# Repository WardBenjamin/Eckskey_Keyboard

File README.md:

# Eckskey

The Eckskey (pronounced "x key") keyboard is an open source 74% mechanical keyboard, designed with an emphasis on electrical correctness and manufacturability, and with some fun tricks.

## Design Philosophy

Throughout the design, electrical correctness will be emphasized, including proper differential pair routing (within the constraints of a two layer design), ground planes, current carrying capacity, and oscillator routing. The board is manufacturable with 6mil trace/space, accomplishable with 1oz two layer designs by local vendors in your area (including the United States) as well as at the cheapest Chinese vendors like JLCPCB, PCBway, and AllPCB.

The base keyboard is designed to be made in two pieces, meaning that it can be assembled in a small/cheap reflow oven like a ControLEO 3 toaster oven conversion or the common Chinese T962 variants. This adds a small amount of BOM cost and would probably increase the cost at quantity, but enables wider access.

This keyboard is NOT meant to be assembled by the typical r/MK hobbyist - it includes QFN and 0603 parts which require a stencil and a pair of tweezers and a pick and place machine to assemble reasonably. You CAN solder these by hand or with hot air but it is difficult. 

## Fun tricks

In total, the base keyboard is a 74% design, meaning that it retains alphanumerics, function keys (F1-F12), and symbols. In addition, the bottom row has been modified to add a left function key (FN) between left control and META/Windows and a right print screen key between menu and right control. Since it still uses a normal 6.25U spacebar, the right keys in the bottom of the row have each been shrunk to 1U. The function keys have been shifted leftwards and collapsed in order to make space for 1U insert and delete keys above backspace. This retains all common functionality of a 100% keyboard except for nav cluster, media keys, and numpad.

The base keyboard includes an integrated USB hub to allow for additional modules to be connected. Two modules will be made - a numpad and nav cluster+media keys. These will technically be separate keyboards, connected via USB-C and magnetic mounting, and can be used standalone as well. These keyboards also have access to the function key by taking advantage of the SBU pins of the USB-C connectors which are normally unused in a USB 1.1/2.0 implementation.

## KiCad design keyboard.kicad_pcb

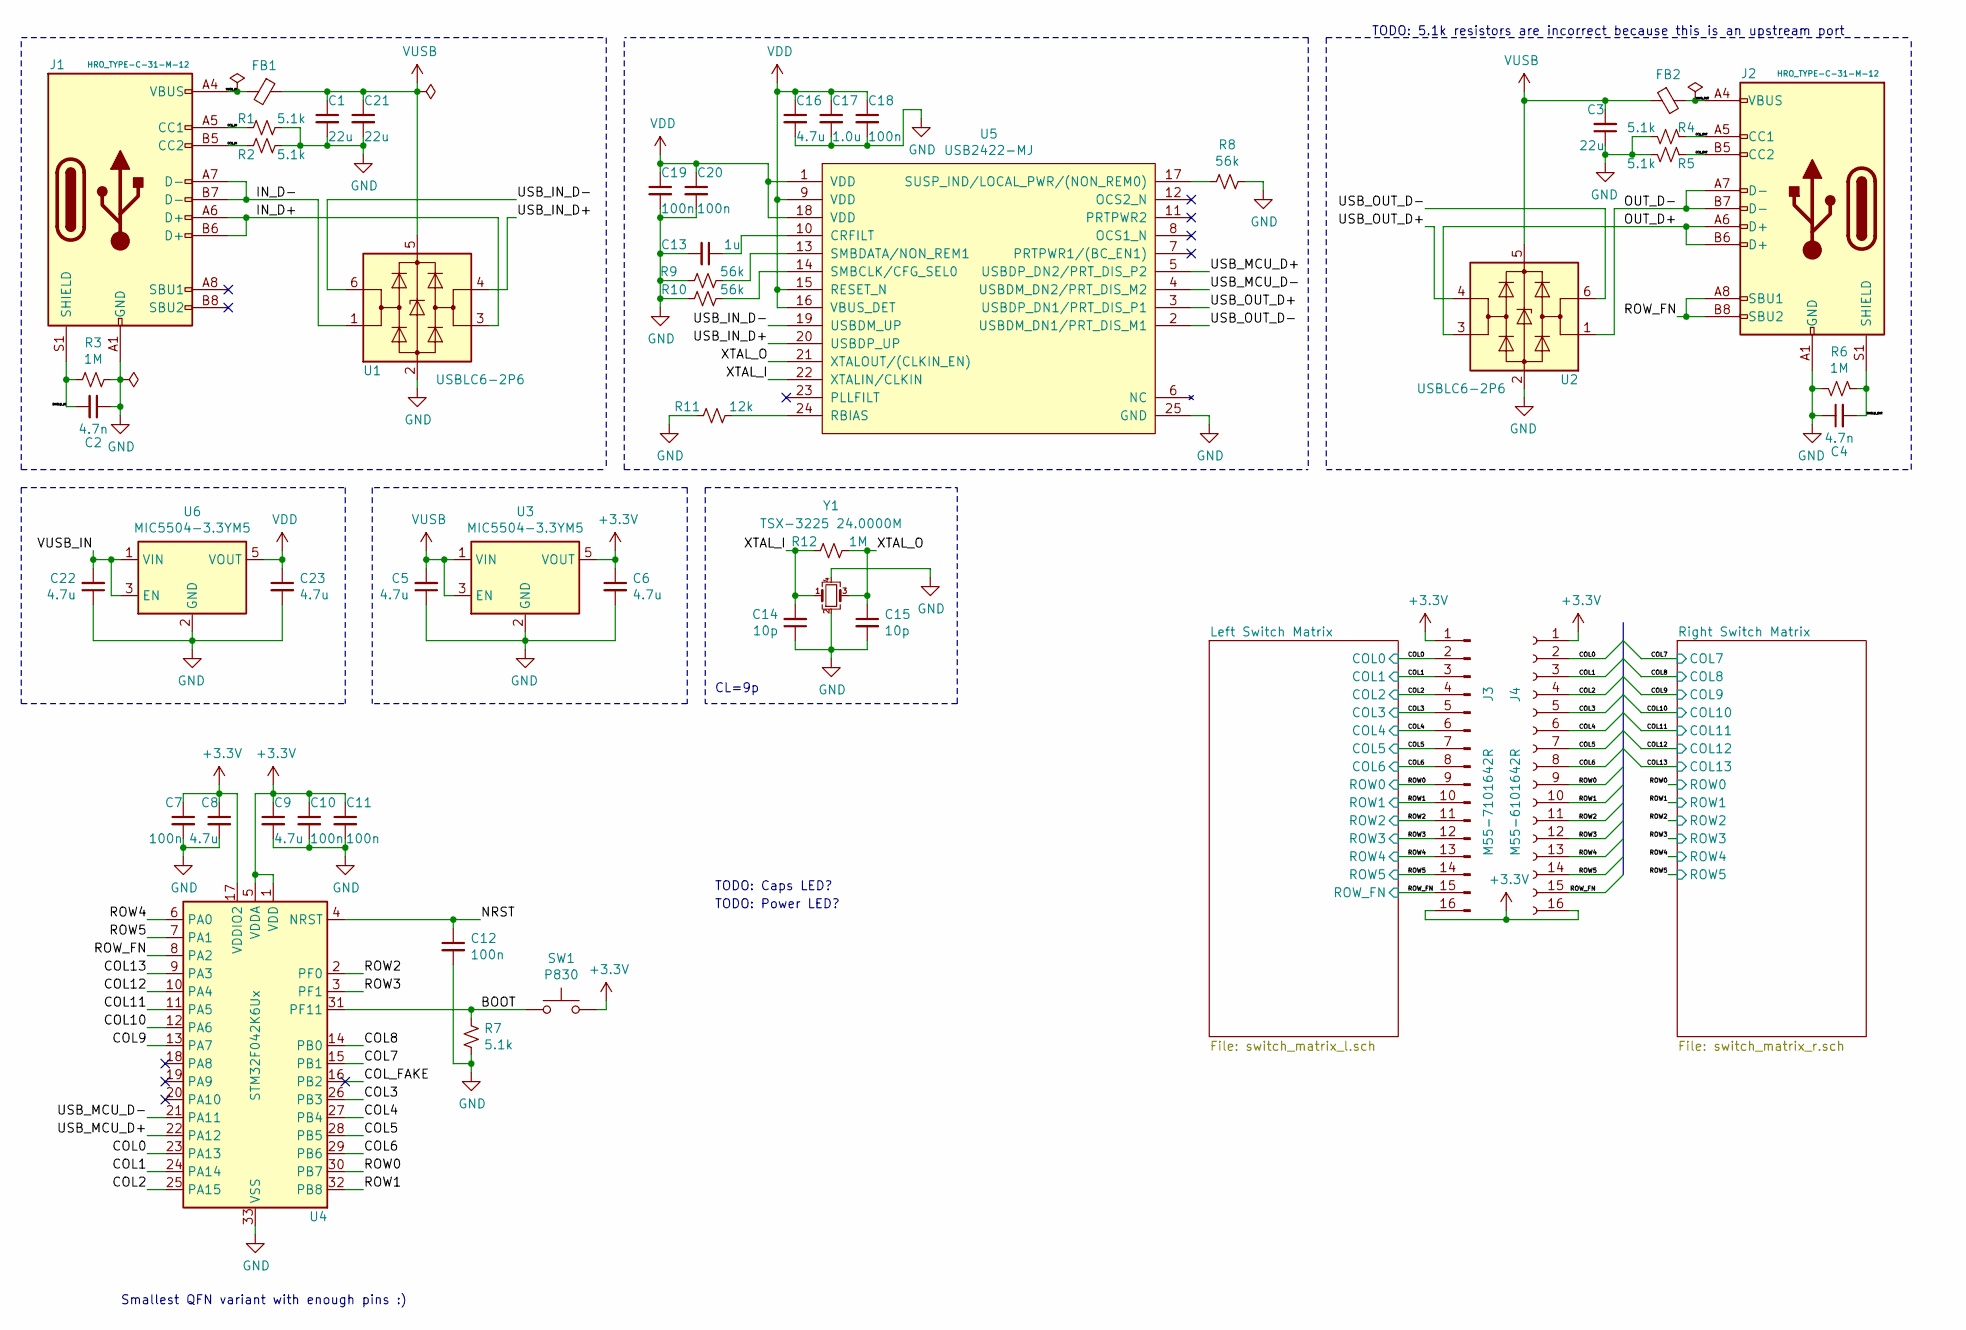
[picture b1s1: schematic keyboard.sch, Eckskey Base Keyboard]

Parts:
C1, C3, C21: 22u; C_0603_1608Metric
C2, C4: 4.7n; C_0603_1608Metric
C5, C6, C8, C9, C16, C22, C23: 4.7u; C_0603_1608Metric
C7, C10, C11, C12, C18, C19, C20: 100n; C_0603_1608Metric
C13: 1u; C_0603_1608Metric
C14, C15: 10p; C_0603_1608Metric
C17: 1.0u; C_0603_1608Metric
FB1, FB2: Ferrite_Bead_Small; L_0603_1608Metric
J1, J2: HRO_TYPE-C-31-M-12; USB_C_Receptacle_HRO_TYPE-C-31-M-12
J3: M55-7101642R; M557101642R
J4: M55-6101642R; M556101642R
R1, R2, R4, R5, R7: 5.1k; R_0603_1608Metric
R3, R6, R12: 1M; R_0603_1608Metric
R8, R9, R10: 56k; R_0603_1608Metric
R11: 12k; R_0603_1608Metric
SW1: P830; SW_SPST_PTS830
U1, U2: USBLC6-2P6; SOT-666
U3, U6: MIC5504-3.3YM5; SOT-23-5
U4: STM32F042K6Ux; QFN-32-1EP_5x5mm_P0.5mm_EP3.45x3.45mm
U5: USB2422-MJ; QFN-24-1EP_4x4mm_P0.5mm_EP2.7x2.7mm_ThermalVias
Y1: TSX-3225 24.0000M; Crystal_SMD_SeikoEpson_TSX3225-4Pin_3.2x2.5mm

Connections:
+3V3: C6.1, C7.1, C8.1, C9.1, C10.1, C11.1, J3.1, J3.16, J4.1, J4.16, SW1.2, U3.5 (VOUT), U4.1 (VDD), U4.5 (VDDA), U4.17 (VDDIO2); also elsewhere on the board
/BOOT: R7.1, SW1.1, U4.31 (PF11)
/CC1_IN: J1.A5 (CC1), R1.2
/CC1_OUT: J2.A5 (CC1), R4.2
/CC2_IN: J1.B5 (CC2), R2.2
/CC2_OUT: J2.B5 (CC2), R5.2
/COL0: J3.2, J4.2, U4.23 (PA13); also elsewhere on the board
/COL1: J3.3, J4.3, U4.24 (PA14); also elsewhere on the board
/COL2: J3.4, J4.4, U4.25 (PA15); also elsewhere on the board
/COL3: J3.5, J4.5, U4.26 (PB3); also elsewhere on the board
/COL4: J3.6, J4.6, U4.27 (PB4); also elsewhere on the board
/COL5: J3.7, J4.7, U4.28 (PB5); also elsewhere on the board
/COL6: J3.8, J4.8, U4.29 (PB6); also elsewhere on the board
/COL7: U4.15 (PB1); also elsewhere on the board
/COL8: U4.14 (PB0); also elsewhere on the board
/COL9: U4.13 (PA7); also elsewhere on the board
/COL10: U4.12 (PA6); also elsewhere on the board
/COL11: U4.11 (PA5); also elsewhere on the board
/COL12: U4.10 (PA4); also elsewhere on the board
/COL13: U4.9 (PA3); also elsewhere on the board
/IN_D+: J1.A6 (D+), J1.B6 (D+), U1.3 (I/O2)
/IN_D-: J1.A7 (D-), J1.B7 (D-), U1.1 (I/O1)
/NRST: C12.1, U4.4 (NRST)
/OUT_D+: J2.A6 (D+), J2.B6 (D+), U2.3 (I/O2)
/OUT_D-: J2.A7 (D-), J2.B7 (D-), U2.1 (I/O1)
/ROW0: J3.9, J4.9, U4.30 (PB7); also elsewhere on the board
/ROW1: J3.10, J4.10, U4.32 (PB8); also elsewhere on the board
/ROW2: J3.11, J4.11, U4.2 (PF0); also elsewhere on the board
/ROW3: J3.12, J4.12, U4.3 (PF1); also elsewhere on the board
/ROW4: J3.13, J4.13, U4.6 (PA0); also elsewhere on the board
/ROW5: J3.14, J4.14, U4.7 (PA1); also elsewhere on the board
/ROW_FN: J2.A8 (SBU1), J2.B8 (SBU2), J3.15, J4.15, U4.8 (PA2); also elsewhere on the board
/SHIELD_IN: C2.2, J1.S1 (SHIELD), R3.2
/SHIELD_OUT: C4.2, J2.S1 (SHIELD), R6.2
/USB_IN_D+: U1.4 (I/O2), U5.20 (USBDP_UP)
/USB_IN_D-: U1.6 (I/O1), U5.19 (USBDM_UP)
/USB_MCU_D+: U4.22 (PA12), U5.5 (USBDP_DN2/PRT_DIS_P2)
/USB_MCU_D-: U4.21 (PA11), U5.4 (USBDM_DN2/PRT_DIS_M2)
/USB_OUT_D+: U2.4 (I/O2), U5.3 (USBDP_DN1/PRT_DIS_P1)
/USB_OUT_D-: U2.6 (I/O1), U5.2 (USBDM_DN1/PRT_DIS_M1)
/VUSB_IN: C22.2, FB1.2, J1.A4 (VBUS), J1.A9 (VBUS), J1.B4 (VBUS), J1.B9 (VBUS), U6.1 (VIN), U6.3 (EN)
/VUSB_OUT: FB2.2, J2.A4 (VBUS), J2.A9 (VBUS), J2.B4 (VBUS), J2.B9 (VBUS)
/XTAL_I: C14.2, R12.2, U5.22 (XTALIN/CLKIN), Y1.1
/XTAL_O: C15.1, R12.1, U5.21 (XTALOUT/(CLKIN_EN)), Y1.3
GND: C1.2, C2.1, C3.1, C4.1, C5.1, C6.2, C7.2, C8.2, C9.2, C10.2, C11.2, C12.2, C13.2, C14.1, C15.2, C16.2, C17.2, C18.2, C19.2, C20.2, C21.2, C22.1, C23.2, J1.A1 (GND), J1.A12 (GND), J1.B1 (GND), J1.B12 (GND), J2.A1 (GND), J2.A12 (GND), J2.B1 (GND), J2.B12 (GND), R1.1, R2.1, R3.1, R4.1, R5.1, R6.1, R7.2, R8.1, R9.2, R10.2, R11.2, U1.2 (GND), U2.2 (GND), U3.2 (GND), U4.33 (VSS), U5.25 (GND), U6.2 (GND), Y1.2, Y1.4
unnamed: C13.1, U5.10 (CRFILT)
unnamed: R8.2, U5.17 (SUSP_IND/LOCAL_PWR/(NON_REM0))
unnamed: R9.1, U5.13 (SMBDATA/NON_REM1)
unnamed: R10.1, U5.14 (SMBCLK/CFG_SEL0)
unnamed: R11.1, U5.24 (RBIAS)
VDD: C16.1, C17.1, C18.1, C19.1, C20.1, C23.1, U5.1 (VDD), U5.9 (VDD), U5.15 (RESET_N), U5.16 (VBUS_DET), U5.18 (VDD), U6.5 (VOUT)
VUSB: C1.1, C3.2, C5.2, C21.1, FB1.1, FB2.1, U1.5 (VBUS), U2.5 (VBUS), U3.1 (VIN), U3.3 (EN)

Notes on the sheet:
Smallest QFN variant with enough pins :)
CL=9p
TODO: Caps LED?
TODO: 5.1k resistors are incorrect because this is an upstream port
TODO: Power LED?

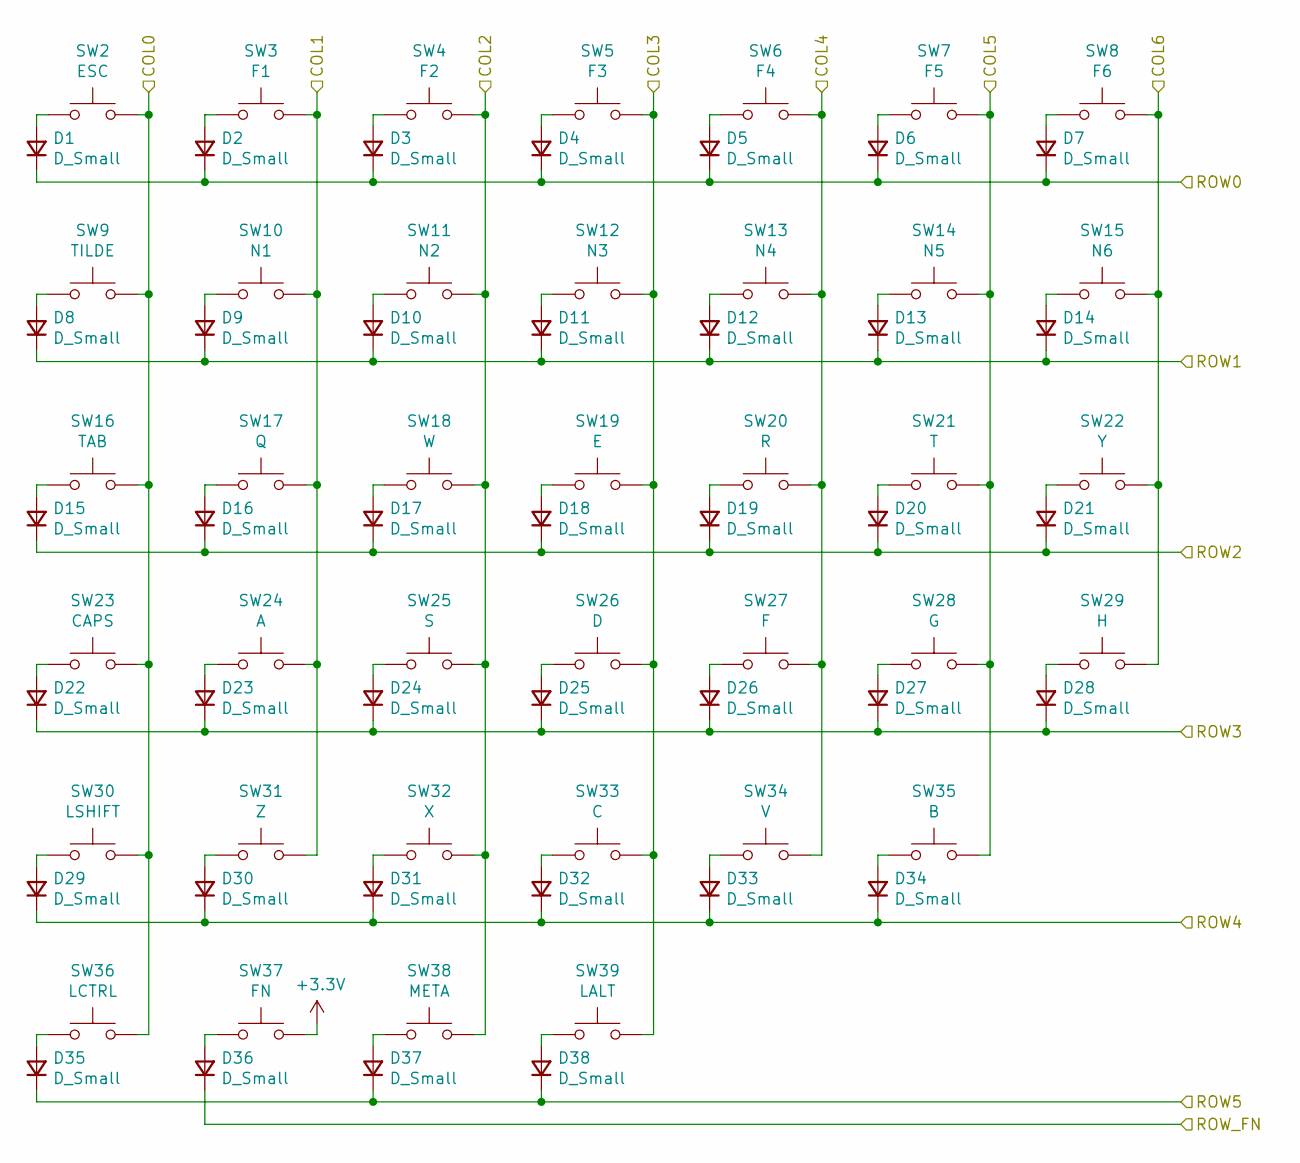
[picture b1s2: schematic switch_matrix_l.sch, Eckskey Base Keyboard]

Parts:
D1, D2, D3, D4, D5, D6, D7, D8, D9, D10, D11, D12, D13, D14, D15, D16, D17, D18, D19, D20, D21, D22, D23, D24, D25, D26, D27, D28, D29, D30, D31, D32, D33, D34, D35, D36, D37, D38: D_Small; D_SOD-123F
SW2: ESC; MX-1U
SW3: F1; MX-1U
SW4: F2; MX-1U
SW5: F3; MX-1U
SW6: F4; MX-1U
SW7: F5; MX-1U
SW8: F6; MX-1U
SW9: TILDE; MX-1U
SW10: N1; MX-1U
SW11: N2; MX-1U
SW12: N3; MX-1U
SW13: N4; MX-1U
SW14: N5; MX-1U
SW15: N6; MX-1U
SW16: TAB; MX-1.5U
SW17: Q; MX-1U
SW18: W; MX-1U
SW19: E; MX-1U
SW20: R; MX-1U
SW21: T; MX-1U
SW22: Y; MX-1U
SW23: CAPS; MX-1.75U
SW24: A; MX-1U
SW25: S; MX-1U
SW26: D; MX-1U
SW27: F; MX-1U
SW28: G; MX-1U
SW29: H; MX-1U
SW30: LSHIFT; MX-2.25U
SW31: Z; MX-1U
SW32: X; MX-1U
SW33: C; MX-1U
SW34: V; MX-1U
SW35: B; MX-1U
SW36: LCTRL; MX-1.25U
SW37: FN; MX-1U
SW38: META; MX-1.25U
SW39: LALT; MX-1.25U

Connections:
+3V3: SW37.2; also elsewhere on the board
/COL0: SW2.2, SW9.2, SW16.2, SW23.2, SW30.2, SW36.2; also elsewhere on the board
/COL1: SW3.2, SW10.2, SW17.2, SW24.2, SW31.2; also elsewhere on the board
/COL2: SW4.2, SW11.2, SW18.2, SW25.2, SW32.2, SW38.2; also elsewhere on the board
/COL3: SW5.2, SW12.2, SW19.2, SW26.2, SW33.2, SW39.2; also elsewhere on the board
/COL4: SW6.2, SW13.2, SW20.2, SW27.2, SW34.2; also elsewhere on the board
/COL5: SW7.2, SW14.2, SW21.2, SW28.2, SW35.2; also elsewhere on the board
/COL6: SW8.2, SW15.2, SW22.2, SW29.2; also elsewhere on the board
/ROW0: D1.1 (K), D2.1 (K), D3.1 (K), D4.1 (K), D5.1 (K), D6.1 (K), D7.1 (K); also elsewhere on the board
/ROW1: D8.1 (K), D9.1 (K), D10.1 (K), D11.1 (K), D12.1 (K), D13.1 (K), D14.1 (K); also elsewhere on the board
/ROW2: D15.1 (K), D16.1 (K), D17.1 (K), D18.1 (K), D19.1 (K), D20.1 (K), D21.1 (K); also elsewhere on the board
/ROW3: D22.1 (K), D23.1 (K), D24.1 (K), D25.1 (K), D26.1 (K), D27.1 (K), D28.1 (K); also elsewhere on the board
/ROW4: D29.1 (K), D30.1 (K), D31.1 (K), D32.1 (K), D33.1 (K), D34.1 (K); also elsewhere on the board
/ROW5: D35.1 (K), D37.1 (K), D38.1 (K); also elsewhere on the board
/ROW_FN: D36.1 (K); also elsewhere on the board
unnamed: D1.2 (A), SW2.1
unnamed: D2.2 (A), SW3.1
unnamed: D3.2 (A), SW4.1
unnamed: D4.2 (A), SW5.1
unnamed: D5.2 (A), SW6.1
unnamed: D6.2 (A), SW7.1
unnamed: D7.2 (A), SW8.1
unnamed: D8.2 (A), SW9.1
unnamed: D9.2 (A), SW10.1
unnamed: D10.2 (A), SW11.1
unnamed: D11.2 (A), SW12.1
unnamed: D12.2 (A), SW13.1
unnamed: D13.2 (A), SW14.1
unnamed: D14.2 (A), SW15.1
unnamed: D15.2 (A), SW16.1
unnamed: D16.2 (A), SW17.1
unnamed: D17.2 (A), SW18.1
unnamed: D18.2 (A), SW19.1
unnamed: D19.2 (A), SW20.1
unnamed: D20.2 (A), SW21.1
unnamed: D21.2 (A), SW22.1
unnamed: D22.2 (A), SW23.1
unnamed: D23.2 (A), SW24.1
unnamed: D24.2 (A), SW25.1
unnamed: D25.2 (A), SW26.1
unnamed: D26.2 (A), SW27.1
unnamed: D27.2 (A), SW28.1
unnamed: D28.2 (A), SW29.1
unnamed: D29.2 (A), SW30.1
unnamed: D30.2 (A), SW31.1
unnamed: D31.2 (A), SW32.1
unnamed: D32.2 (A), SW33.1
unnamed: D33.2 (A), SW34.1
unnamed: D34.2 (A), SW35.1
unnamed: D35.2 (A), SW36.1
unnamed: D36.2 (A), SW37.1
unnamed: D37.2 (A), SW38.1
unnamed: D38.2 (A), SW39.1

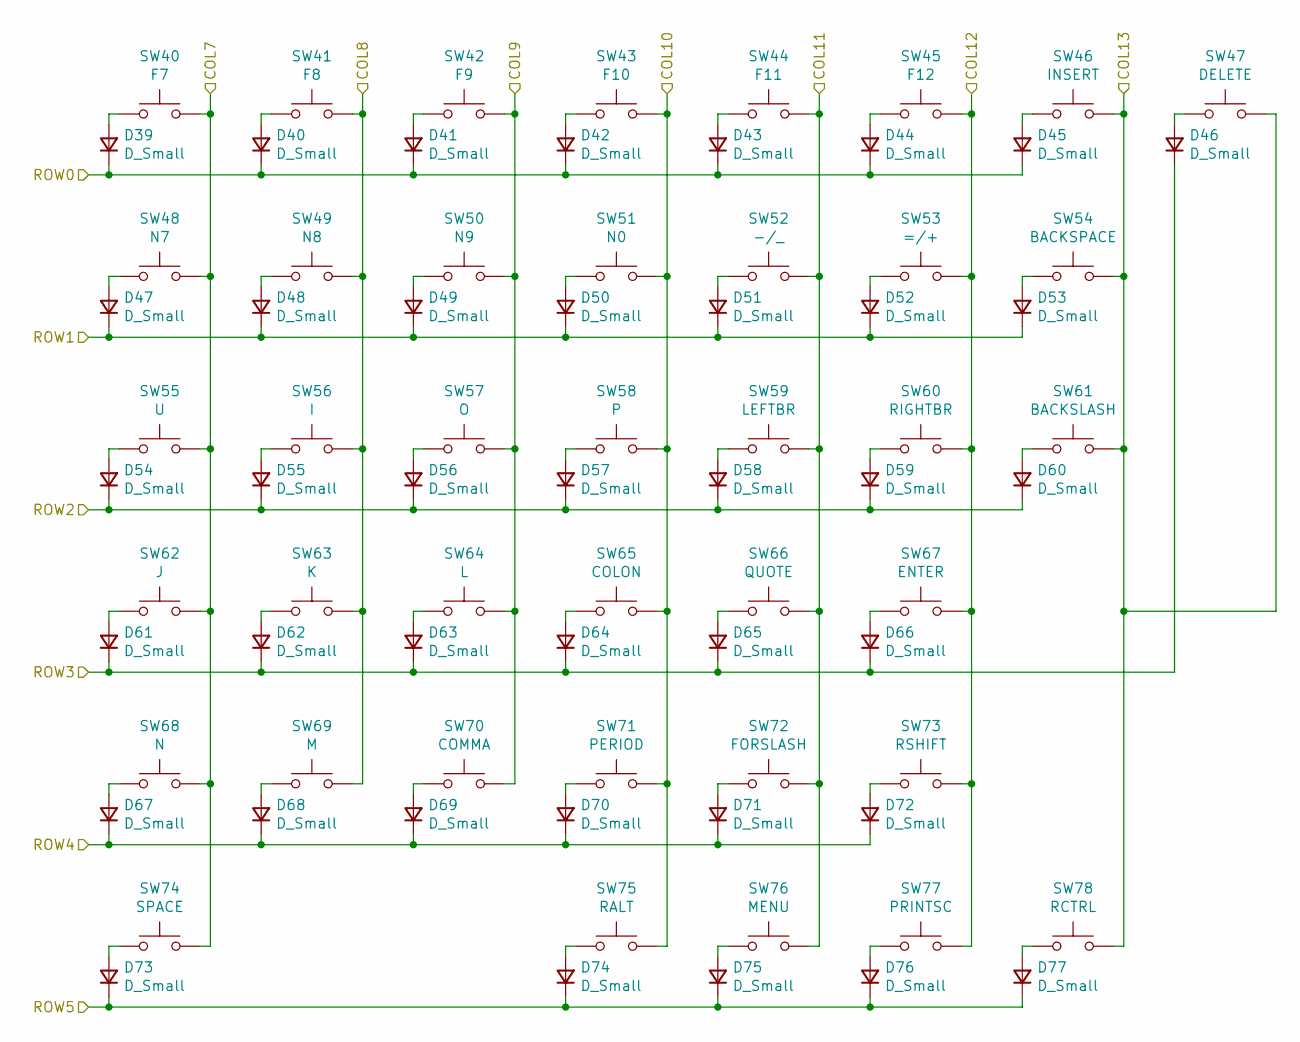
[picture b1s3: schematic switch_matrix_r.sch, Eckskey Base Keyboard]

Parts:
D39, D40, D41, D42, D43, D44, D45, D46, D47, D48, D49, D50, D51, D52, D53, D54, D55, D56, D57, D58, D59, D60, D61, D62, D63, D64, D65, D66, D67, D68, D69, D70, D71, D72, D73, D74, D75, D76, D77: D_Small; D_SOD-123F
SW40: F7; MX-1U
SW41: F8; MX-1U
SW42: F9; MX-1U
SW43: F10; MX-1U
SW44: F11; MX-1U
SW45: F12; MX-1U
SW46: INSERT; MX-1U
SW47: DELETE; MX-1U
SW48: N7; MX-1U
SW49: N8; MX-1U
SW50: N9; MX-1U
SW51: N0; MX-1U
SW52: -/_; MX-1U
SW53: =/+; MX-1U
SW54: BACKSPACE; MX-2U
SW55: U; MX-1U
SW56: I; MX-1U
SW57: O; MX-1U
SW58: P; MX-1U
SW59: LEFTBR; MX-1U
SW60: RIGHTBR; MX-1U
SW61: BACKSLASH; MX-1.5U
SW62: J; MX-1U
SW63: K; MX-1U
SW64: L; MX-1U
SW65: COLON; MX-1U
SW66: QUOTE; MX-1U
SW67: ENTER; MX-2.25U
SW68: N; MX-1U
SW69: M; MX-1U
SW70: COMMA; MX-1U
SW71: PERIOD; MX-1U
SW72: FORSLASH; MX-1U
SW73: RSHIFT; MX-2.75U
SW74: SPACE; MX-6.25U
SW75: RALT; MX-1U
SW76: MENU; MX-1U
SW77: PRINTSC; MX-1U
SW78: RCTRL; MX-1U

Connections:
/COL7: SW40.2, SW48.2, SW55.2, SW62.2, SW68.2, SW74.2; also elsewhere on the board
/COL8: SW41.2, SW49.2, SW56.2, SW63.2, SW69.2; also elsewhere on the board
/COL9: SW42.2, SW50.2, SW57.2, SW64.2, SW70.2; also elsewhere on the board
/COL10: SW43.2, SW51.2, SW58.2, SW65.2, SW71.2, SW75.2; also elsewhere on the board
/COL11: SW44.2, SW52.2, SW59.2, SW66.2, SW72.2, SW76.2; also elsewhere on the board
/COL12: SW45.2, SW53.2, SW60.2, SW67.2, SW73.2, SW77.2; also elsewhere on the board
/COL13: SW46.2, SW47.2, SW54.2, SW61.2, SW78.2; also elsewhere on the board
/ROW0: D39.1 (K), D40.1 (K), D41.1 (K), D42.1 (K), D43.1 (K), D44.1 (K), D45.1 (K); also elsewhere on the board
/ROW1: D47.1 (K), D48.1 (K), D49.1 (K), D50.1 (K), D51.1 (K), D52.1 (K), D53.1 (K); also elsewhere on the board
/ROW2: D54.1 (K), D55.1 (K), D56.1 (K), D57.1 (K), D58.1 (K), D59.1 (K), D60.1 (K); also elsewhere on the board
/ROW3: D46.1 (K), D61.1 (K), D62.1 (K), D63.1 (K), D64.1 (K), D65.1 (K), D66.1 (K); also elsewhere on the board
/ROW4: D67.1 (K), D68.1 (K), D69.1 (K), D70.1 (K), D71.1 (K), D72.1 (K); also elsewhere on the board
/ROW5: D73.1 (K), D74.1 (K), D75.1 (K), D76.1 (K), D77.1 (K); also elsewhere on the board
unnamed: D39.2 (A), SW40.1
unnamed: D40.2 (A), SW41.1
unnamed: D41.2 (A), SW42.1
unnamed: D42.2 (A), SW43.1
unnamed: D43.2 (A), SW44.1
unnamed: D44.2 (A), SW45.1
unnamed: D45.2 (A), SW46.1
unnamed: D46.2 (A), SW47.1
unnamed: D47.2 (A), SW48.1
unnamed: D48.2 (A), SW49.1
unnamed: D49.2 (A), SW50.1
unnamed: D50.2 (A), SW51.1
unnamed: D51.2 (A), SW52.1
unnamed: D52.2 (A), SW53.1
unnamed: D53.2 (A), SW54.1
unnamed: D54.2 (A), SW55.1
unnamed: D55.2 (A), SW56.1
unnamed: D56.2 (A), SW57.1
unnamed: D57.2 (A), SW58.1
unnamed: D58.2 (A), SW59.1
unnamed: D59.2 (A), SW60.1
unnamed: D60.2 (A), SW61.1
unnamed: D61.2 (A), SW62.1
unnamed: D62.2 (A), SW63.1
unnamed: D63.2 (A), SW64.1
unnamed: D64.2 (A), SW65.1
unnamed: D65.2 (A), SW66.1
unnamed: D66.2 (A), SW67.1
unnamed: D67.2 (A), SW68.1
unnamed: D68.2 (A), SW69.1
unnamed: D69.2 (A), SW70.1
unnamed: D70.2 (A), SW71.1
unnamed: D71.2 (A), SW72.1
unnamed: D72.2 (A), SW73.1
unnamed: D73.2 (A), SW74.1
unnamed: D74.2 (A), SW75.1
unnamed: D75.2 (A), SW76.1
unnamed: D76.2 (A), SW77.1
unnamed: D77.2 (A), SW78.1

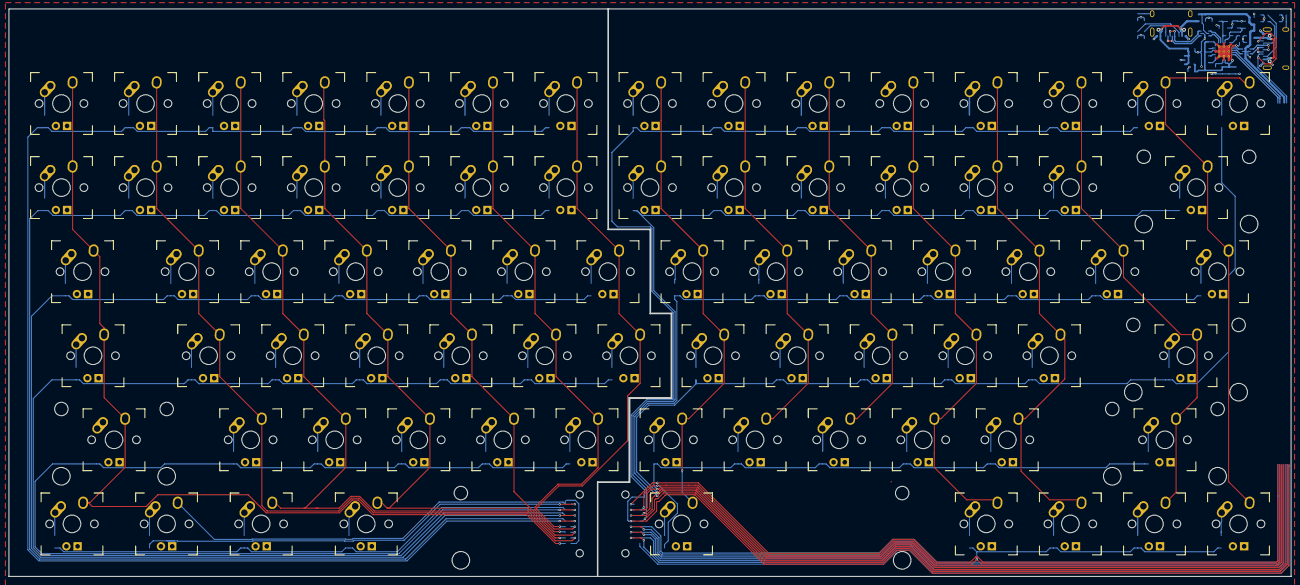
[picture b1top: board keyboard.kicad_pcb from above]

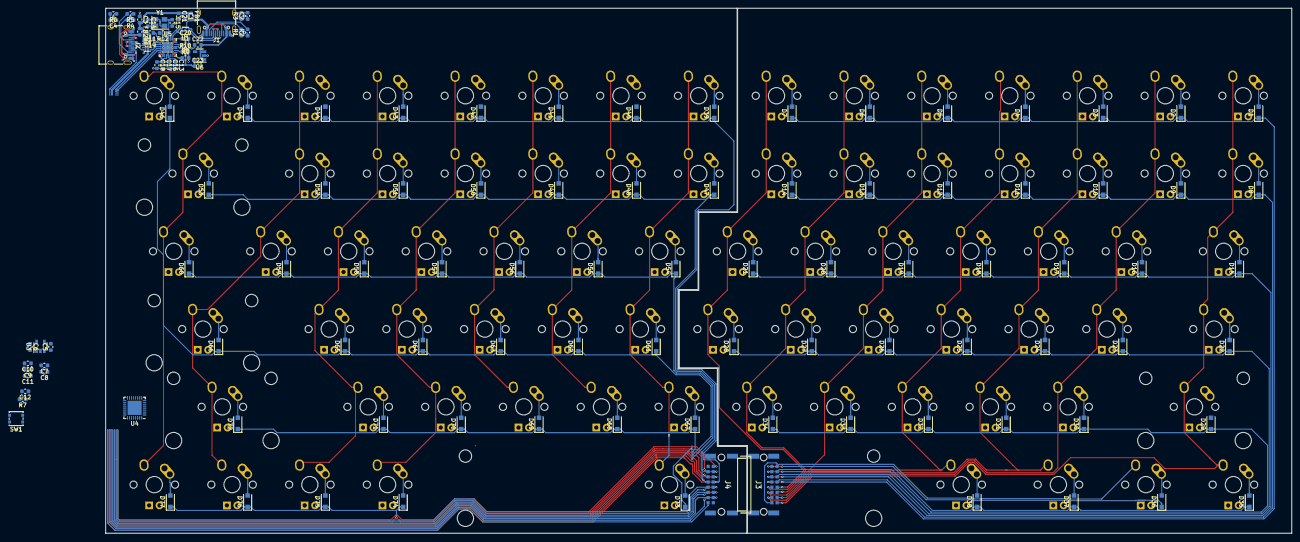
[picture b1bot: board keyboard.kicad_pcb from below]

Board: 2 copper layers, 290.5 x 128.6 mm, 203 parts (126 on the bottom side), 129 nets.

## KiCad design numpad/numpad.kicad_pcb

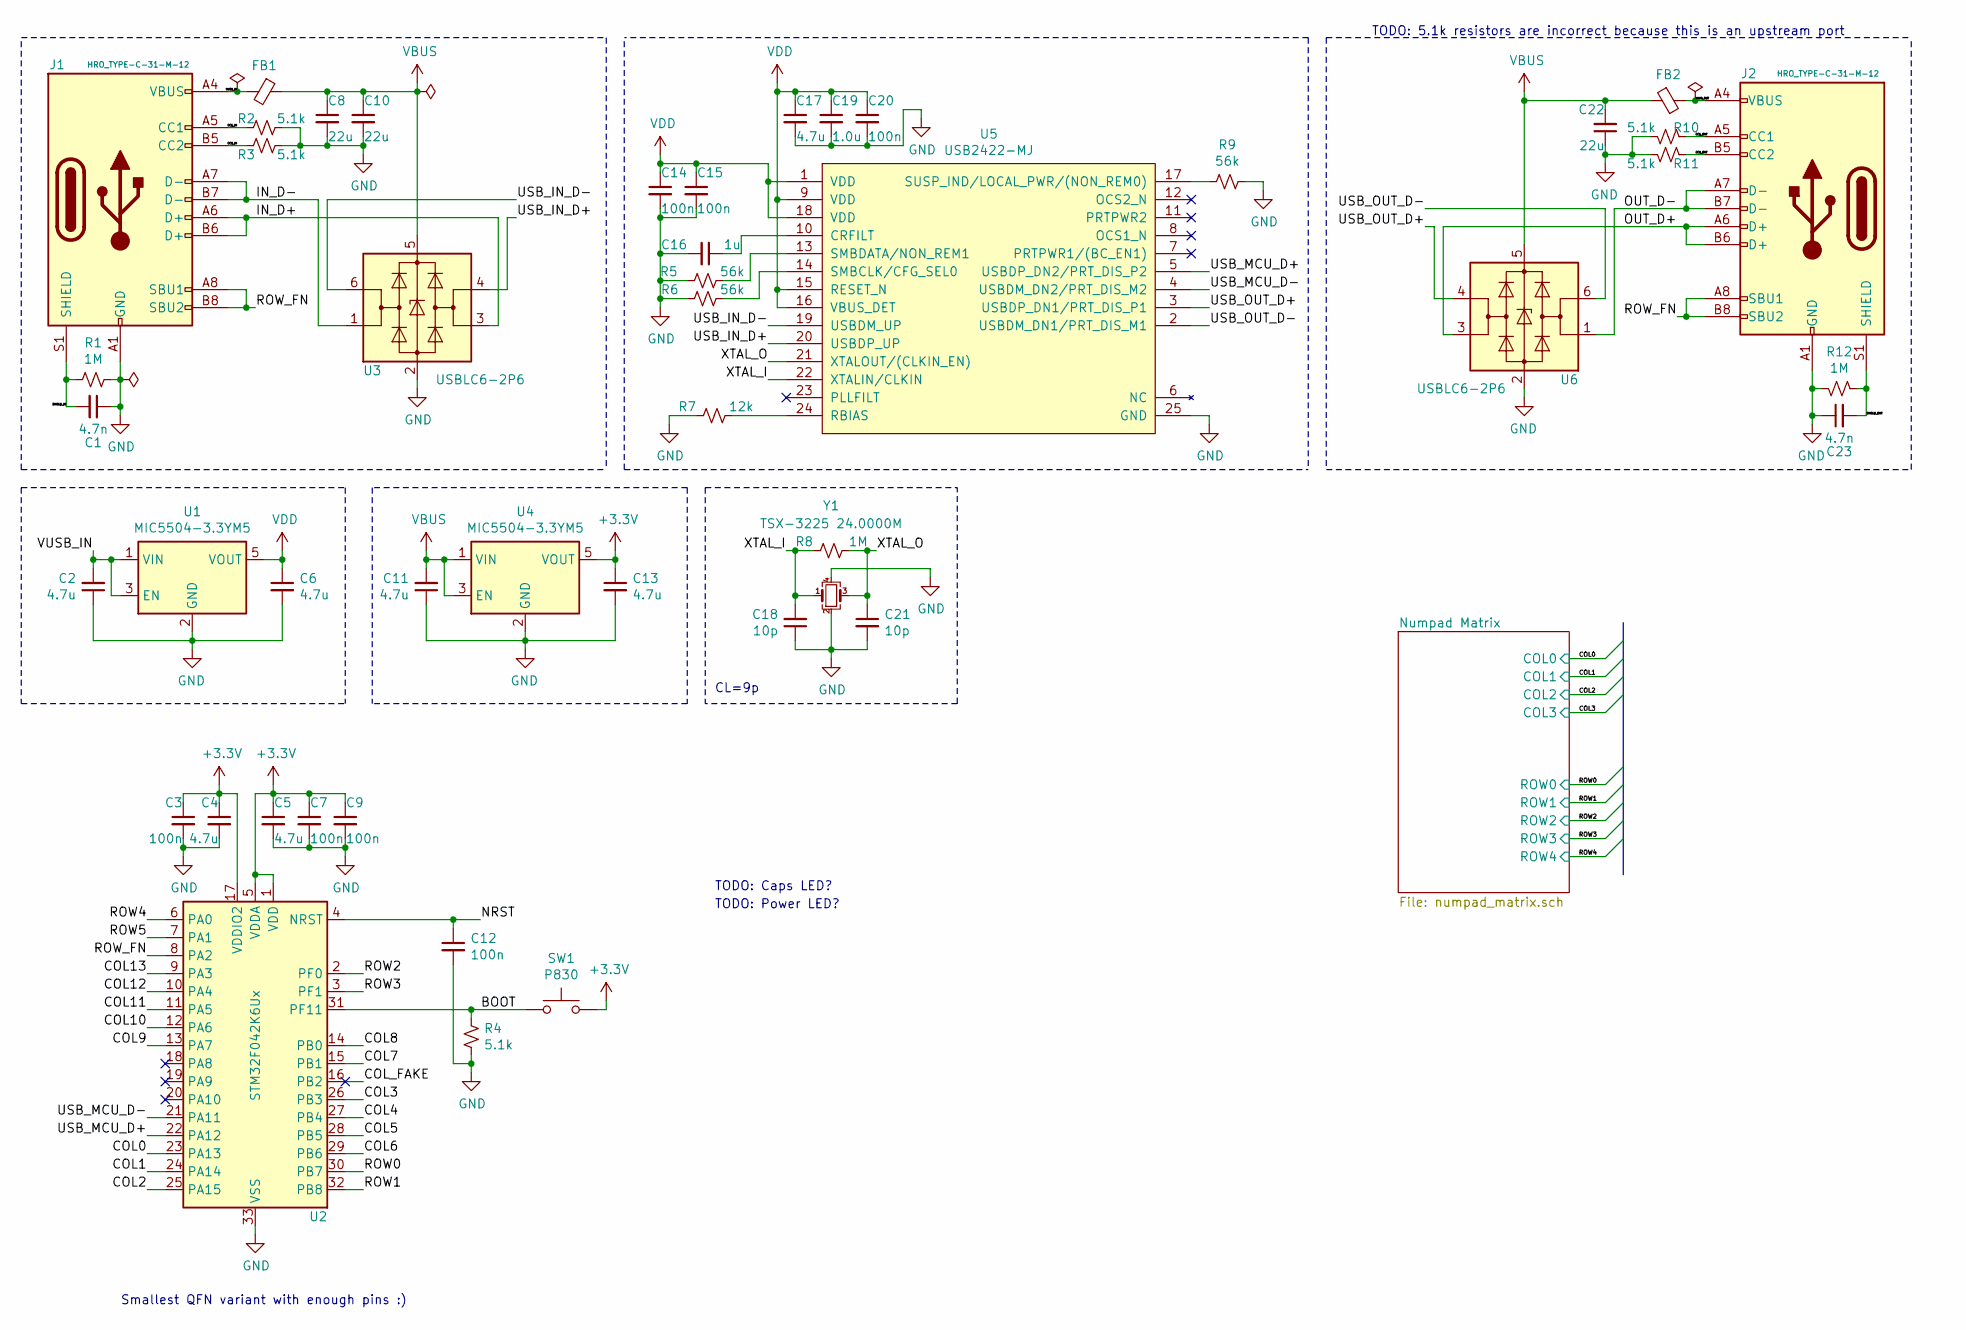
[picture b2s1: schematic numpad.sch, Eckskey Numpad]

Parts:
C1, C23: 4.7n; C_0603_1608Metric
C2, C4, C5, C6, C11, C13, C17: 4.7u; C_0603_1608Metric
C3, C7, C9, C12, C14, C15, C20: 100n; C_0603_1608Metric
C8, C10, C22: 22u; C_0603_1608Metric
C16: 1u; C_0603_1608Metric
C18, C21: 10p; C_0603_1608Metric
C19: 1.0u; C_0603_1608Metric
FB1, FB2: Ferrite_Bead_Small; L_0603_1608Metric
J1, J2: HRO_TYPE-C-31-M-12; USB_C_Receptacle_HRO_TYPE-C-31-M-12
R1, R8, R12: 1M; R_0603_1608Metric
R2, R3, R4, R10, R11: 5.1k; R_0603_1608Metric
R5, R6, R9: 56k; R_0603_1608Metric
R7: 12k; R_0603_1608Metric
SW1: P830; SW_SPST_PTS830
U1, U4: MIC5504-3.3YM5; SOT-23-5
U2: STM32F042K6Ux; QFN-32-1EP_5x5mm_P0.5mm_EP3.45x3.45mm
U3, U6: USBLC6-2P6; SOT-666
U5: USB2422-MJ; QFN-24-1EP_4x4mm_P0.5mm_EP2.7x2.7mm_ThermalVias
Y1: TSX-3225 24.0000M; Crystal_SMD_SeikoEpson_TSX3225-4Pin_3.2x2.5mm

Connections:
+3V3: C3.1, C4.1, C5.1, C7.1, C9.1, C13.1, SW1.2, U2.1 (VDD), U2.5 (VDDA), U2.17 (VDDIO2), U4.5 (VOUT)
/BOOT: R4.1, SW1.1, U2.31 (PF11)
/CC1_IN: J1.A5 (CC1), R2.2
/CC1_OUT: J2.A5 (CC1), R10.2
/CC2_IN: J1.B5 (CC2), R3.2
/CC2_OUT: J2.B5 (CC2), R11.2
/COL0: U2.23 (PA13); also elsewhere on the board
/COL1: U2.24 (PA14); also elsewhere on the board
/COL2: U2.25 (PA15); also elsewhere on the board
/COL3: U2.26 (PB3); also elsewhere on the board
/COL4: U2.27 (PB4)
/COL5: U2.28 (PB5)
/COL6: U2.29 (PB6)
/COL7: U2.15 (PB1)
/COL8: U2.14 (PB0)
/COL9: U2.13 (PA7)
/COL10: U2.12 (PA6)
/COL11: U2.11 (PA5)
/COL12: U2.10 (PA4)
/COL13: U2.9 (PA3)
/COL_FAKE: U2.16 (PB2)
/IN_D+: J1.A6 (D+), J1.B6 (D+), U3.3 (I/O2)
/IN_D-: J1.A7 (D-), J1.B7 (D-), U3.1 (I/O1)
/NRST: C12.1, U2.4 (NRST)
/OUT_D+: J2.A6 (D+), J2.B6 (D+), U6.3 (I/O2)
/OUT_D-: J2.A7 (D-), J2.B7 (D-), U6.1 (I/O1)
/ROW0: U2.30 (PB7); also elsewhere on the board
/ROW1: U2.32 (PB8); also elsewhere on the board
/ROW2: U2.2 (PF0); also elsewhere on the board
/ROW3: U2.3 (PF1); also elsewhere on the board
/ROW4: U2.6 (PA0); also elsewhere on the board
/ROW5: U2.7 (PA1)
/ROW_FN: J1.A8 (SBU1), J1.B8 (SBU2), J2.A8 (SBU1), J2.B8 (SBU2), U2.8 (PA2)
/SHIELD_IN: C1.2, J1.S1 (SHIELD), R1.2
/SHIELD_OUT: C23.2, J2.S1 (SHIELD), R12.2
/USB_IN_D+: U3.4 (I/O2), U5.20 (USBDP_UP)
/USB_IN_D-: U3.6 (I/O1), U5.19 (USBDM_UP)
/USB_MCU_D+: U2.22 (PA12), U5.5 (USBDP_DN2/PRT_DIS_P2)
/USB_MCU_D-: U2.21 (PA11), U5.4 (USBDM_DN2/PRT_DIS_M2)
/USB_OUT_D+: U5.3 (USBDP_DN1/PRT_DIS_P1), U6.4 (I/O2)
/USB_OUT_D-: U5.2 (USBDM_DN1/PRT_DIS_M1), U6.6 (I/O1)
/VUSB_IN: C2.2, FB1.2, J1.A4 (VBUS), J1.A9 (VBUS), J1.B4 (VBUS), J1.B9 (VBUS), U1.1 (VIN), U1.3 (EN)
/VUSB_OUT: FB2.2, J2.A4 (VBUS), J2.A9 (VBUS), J2.B4 (VBUS), J2.B9 (VBUS)
/XTAL_I: C18.2, R8.2, U5.22 (XTALIN/CLKIN), Y1.1
/XTAL_O: C21.1, R8.1, U5.21 (XTALOUT/(CLKIN_EN)), Y1.3
GND: C1.1, C2.1, C3.2, C4.2, C5.2, C6.2, C7.2, C8.2, C9.2, C10.2, C11.1, C12.2, C13.2, C14.2, C15.2, C16.2, C17.2, C18.1, C19.2, C20.2, C21.2, C22.1, C23.1, J1.A1 (GND), J1.A12 (GND), J1.B1 (GND), J1.B12 (GND), J2.A1 (GND), J2.A12 (GND), J2.B1 (GND), J2.B12 (GND), R1.1, R2.1, R3.1, R4.2, R5.2, R6.2, R7.2, R9.1, R10.1, R11.1, R12.1, U1.2 (GND), U2.33 (VSS), U3.2 (GND), U4.2 (GND), U5.25 (GND), U6.2 (GND), Y1.2, Y1.4
unnamed: C16.1, U5.10 (CRFILT)
unnamed: R5.1, U5.13 (SMBDATA/NON_REM1)
unnamed: R6.1, U5.14 (SMBCLK/CFG_SEL0)
unnamed: R7.1, U5.24 (RBIAS)
unnamed: R9.2, U5.17 (SUSP_IND/LOCAL_PWR/(NON_REM0))
VBUS: C8.1, C10.1, C11.2, C22.2, FB1.1, FB2.1, U3.5 (VBUS), U4.1 (VIN), U4.3 (EN), U6.5 (VBUS)
VDD: C6.1, C14.1, C15.1, C17.1, C19.1, C20.1, U1.5 (VOUT), U5.1 (VDD), U5.9 (VDD), U5.15 (RESET_N), U5.16 (VBUS_DET), U5.18 (VDD)

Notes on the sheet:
Smallest QFN variant with enough pins :)
CL=9p
TODO: Caps LED?
TODO: 5.1k resistors are incorrect because this is an upstream port
TODO: Power LED?

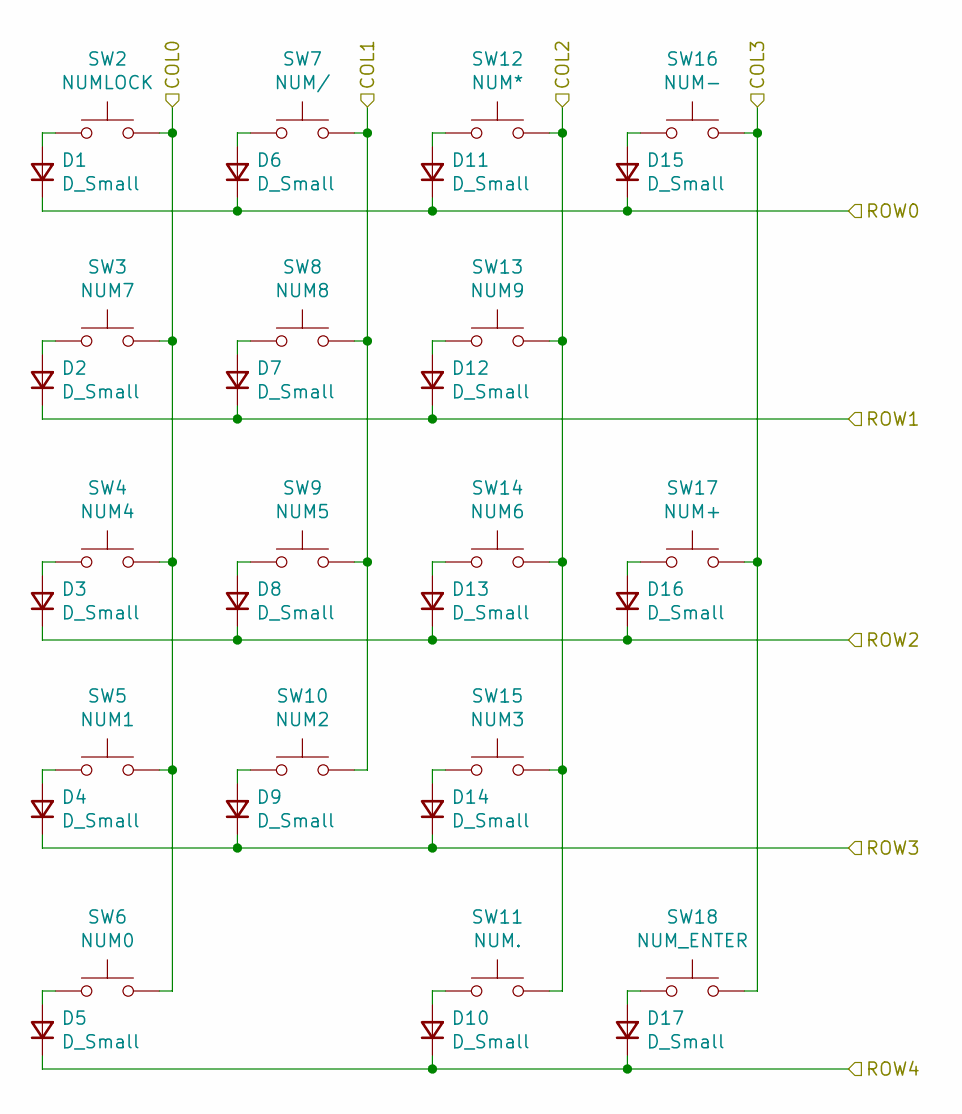
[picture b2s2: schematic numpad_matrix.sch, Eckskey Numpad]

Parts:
D1, D2, D3, D4, D5, D6, D7, D8, D9, D10, D11, D12, D13, D14, D15, D16, D17: D_Small; D_SOD-123F
SW2: NUMLOCK; MX-1U
SW3: NUM7; MX-1U
SW4: NUM4; MX-1U
SW5: NUM1; MX-1U
SW6: NUM0; MX-2U
SW7: NUM/; MX-1U
SW8: NUM8; MX-1U
SW9: NUM5; MX-1U
SW10: NUM2; MX-1U
SW11: NUM.; MX-1U
SW12: NUM*; MX-1U
SW13: NUM9; MX-1U
SW14: NUM6; MX-1U
SW15: NUM3; MX-1U
SW16: NUM-; MX-1U
SW17: NUM+; MX-2U
SW18: NUM_ENTER; MX-2U

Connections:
/COL0: SW2.2, SW3.2, SW4.2, SW5.2, SW6.2; also elsewhere on the board
/COL1: SW7.2, SW8.2, SW9.2, SW10.2; also elsewhere on the board
/COL2: SW11.2, SW12.2, SW13.2, SW14.2, SW15.2; also elsewhere on the board
/COL3: SW16.2, SW17.2, SW18.2; also elsewhere on the board
/ROW0: D1.1 (K), D6.1 (K), D11.1 (K), D15.1 (K); also elsewhere on the board
/ROW1: D2.1 (K), D7.1 (K), D12.1 (K); also elsewhere on the board
/ROW2: D3.1 (K), D8.1 (K), D13.1 (K), D16.1 (K); also elsewhere on the board
/ROW3: D4.1 (K), D9.1 (K), D14.1 (K); also elsewhere on the board
/ROW4: D5.1 (K), D10.1 (K), D17.1 (K); also elsewhere on the board
unnamed: D1.2 (A), SW2.1
unnamed: D2.2 (A), SW3.1
unnamed: D3.2 (A), SW4.1
unnamed: D4.2 (A), SW5.1
unnamed: D5.2 (A), SW6.1
unnamed: D6.2 (A), SW7.1
unnamed: D7.2 (A), SW8.1
unnamed: D8.2 (A), SW9.1
unnamed: D9.2 (A), SW10.1
unnamed: D10.2 (A), SW11.1
unnamed: D11.2 (A), SW12.1
unnamed: D12.2 (A), SW13.1
unnamed: D13.2 (A), SW14.1
unnamed: D14.2 (A), SW15.1
unnamed: D15.2 (A), SW16.1
unnamed: D16.2 (A), SW17.1
unnamed: D17.2 (A), SW18.1
